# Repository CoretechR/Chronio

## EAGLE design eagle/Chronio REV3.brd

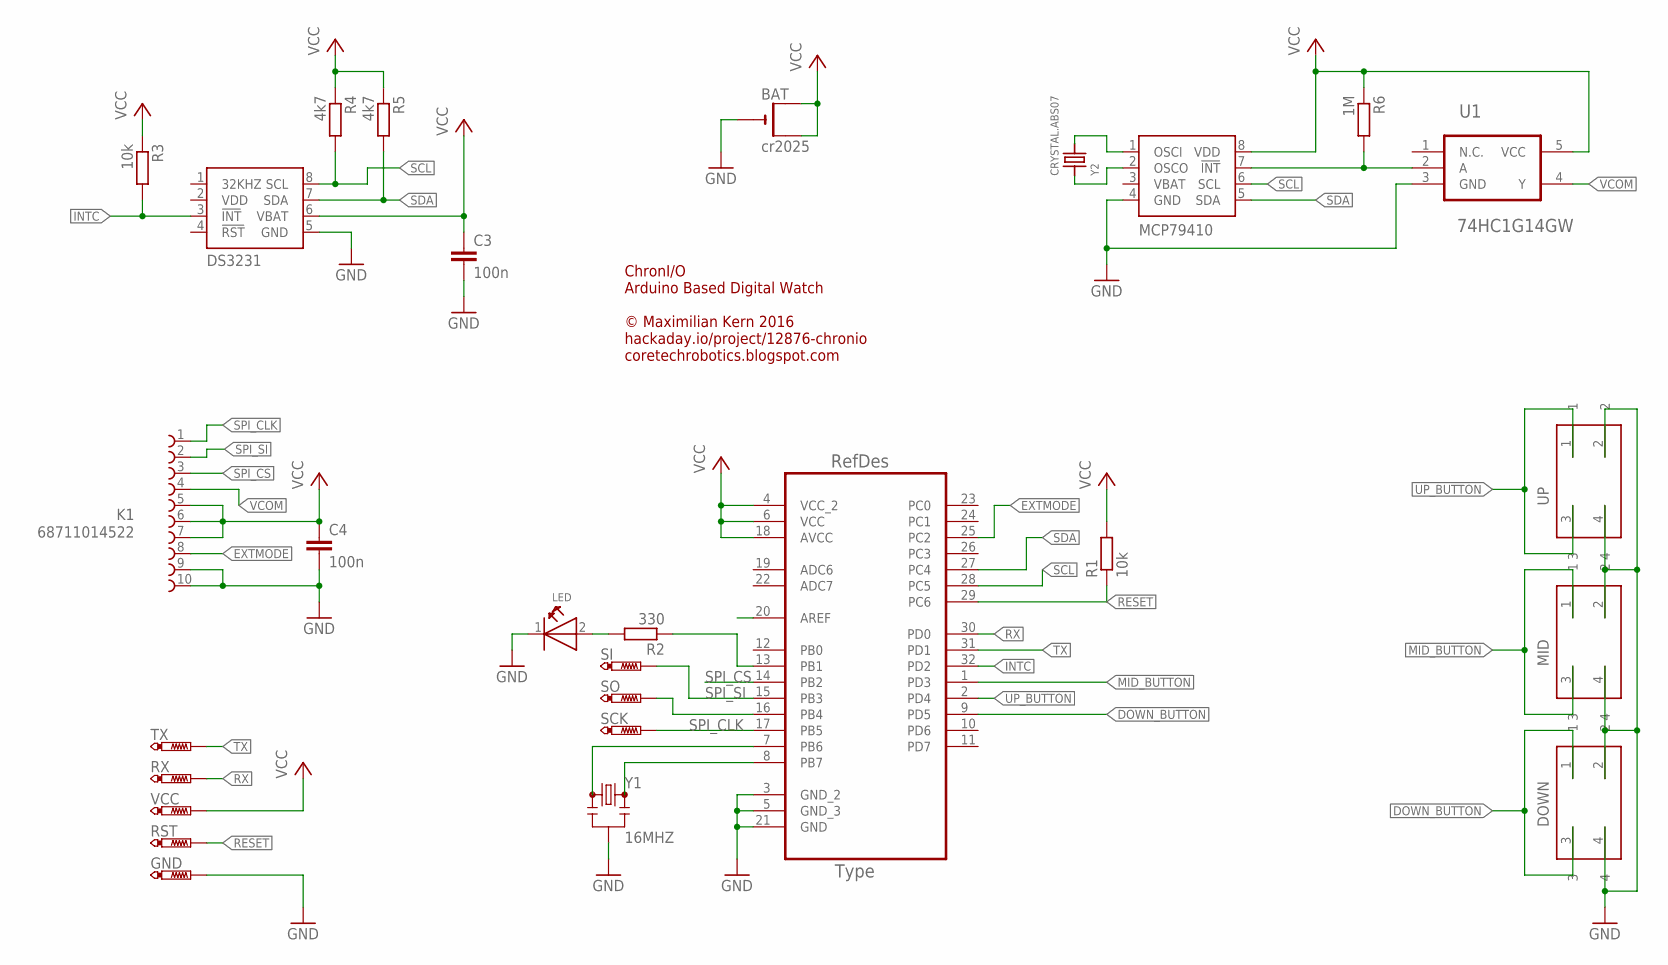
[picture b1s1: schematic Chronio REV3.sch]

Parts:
ATMEGA328P: ATMEGA328P-AU; QFP80P900X900X120-32N
BAT: cr2025; CR2032-SMD
C3, C4: 100n; C0805
DOWN: 434331045822
DS3231: DS3231MLMD; SO08
GND: PTR1TP14SQ; TP14SQ
K1: 68711014522
LED: WL-SMCW-150060GS75000-G; 0603
MCP79410: PCF8523T/1LMD; SO08
MID: 434331045822
R1, R3: 10k; R0805
R2: 330; R0805
R4, R5: 4k7; R0805
R6: 1M; R0805
RST: PTR1TP14SQ; TP14SQ
RX: PTR1TP14SQ; TP14SQ
SCK: PTR1TP14SQ; TP14SQ
SI: PTR1TP14SQ; TP14SQ
SO: PTR1TP14SQ; TP14SQ
TX: PTR1TP14SQ; TP14SQ
U1: 74HC1G14GW; SOT65P210X110-5N
UP: 434331045822
VCC: PTR1TP14SQ; TP14SQ
Y1: 16MHZ; RESONATOR-SMD
Y2: CRYSTAL.ABS07; ABS07

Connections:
AREF: ATMEGA328P.20 (AREF)
DOWN_BUTTON: ATMEGA328P.9 (PD5), DOWN.1, DOWN.3
EXTMODE: ATMEGA328P.25 (PC2), K1.8
GND: ATMEGA328P.3 (GND_2), ATMEGA328P.5 (GND_3), ATMEGA328P.21 (GND), BAT.-, C3.2, C4.2, DOWN.2, DOWN.4, DS3231.5 (GND), GND.TP, K1.9, K1.10, LED.1 (K), MCP79410.4 (GND), MID.2, MID.4, U1.3 (GND), UP.2, UP.4, Y1.2
INTC: ATMEGA328P.32 (PD2), DS3231.3 (!INT), R3.2
MID_BUTTON: ATMEGA328P.1 (PD3), MID.1, MID.3
unnamed: ATMEGA328P.7 (PB6), Y1.1
unnamed: ATMEGA328P.8 (PB7), Y1.3
unnamed: MCP79410.7 (!INT), R6.2, U1.2 (A)
unnamed: ATMEGA328P.16 (PB4), SO.TP
unnamed: MCP79410.1 (OSCI), Y2.2
unnamed: ATMEGA328P.13 (PB1), R2.1
unnamed: LED.2 (A), R2.2
unnamed: MCP79410.2 (OSCO), Y2.1
RESET: ATMEGA328P.29 (PC6), R1.1, RST.TP
RX: ATMEGA328P.30 (PD0), RX.TP
SCL: ATMEGA328P.28 (PC5), DS3231.8 (SCL), MCP79410.6 (SCL), R4.2
SDA: ATMEGA328P.27 (PC4), DS3231.7 (SDA), MCP79410.5 (SDA), R5.2
SPI_CLK: ATMEGA328P.17 (PB5), K1.1, SCK.TP
SPI_CS: ATMEGA328P.14 (PB2), K1.3
SPI_SI: ATMEGA328P.15 (PB3), K1.2, SI.TP
TX: ATMEGA328P.31 (PD1), TX.TP
UP_BUTTON: ATMEGA328P.2 (PD4), UP.1, UP.3
VBAT: MCP79410.3 (VBAT)
VCC: ATMEGA328P.4 (VCC_2), ATMEGA328P.6 (VCC), ATMEGA328P.18 (AVCC), BAT.+$1 (+), BAT.+$2 (+1), C3.1, C4.1, DS3231.6 (VBAT), K1.5, K1.6, K1.7, MCP79410.8 (VDD), R1.2, R3.1, R4.1, R5.1, R6.1, U1.5 (VCC), VCC.TP
VCOM: K1.4, U1.4 (Y)
VDD: DS3231.2 (VDD)

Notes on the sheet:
ChronI/O Arduino Based Digital Watch © Maximilian Kern 2016 hackaday.io/project/12876-chronio coretechrobotics.blogspot.com

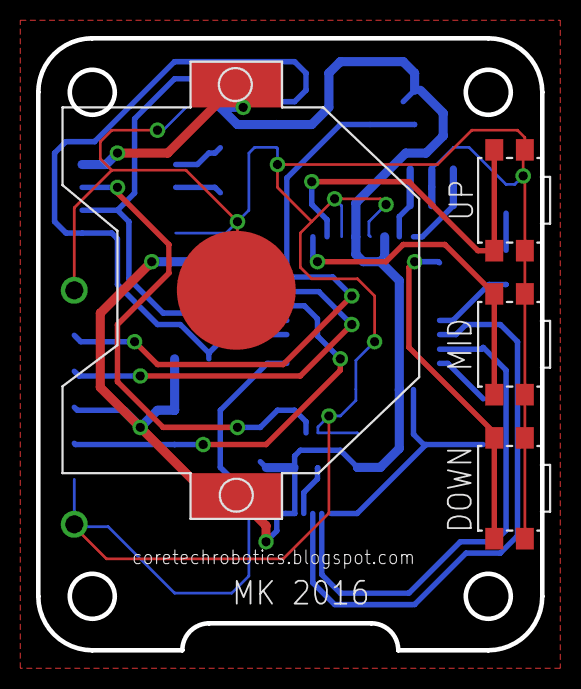
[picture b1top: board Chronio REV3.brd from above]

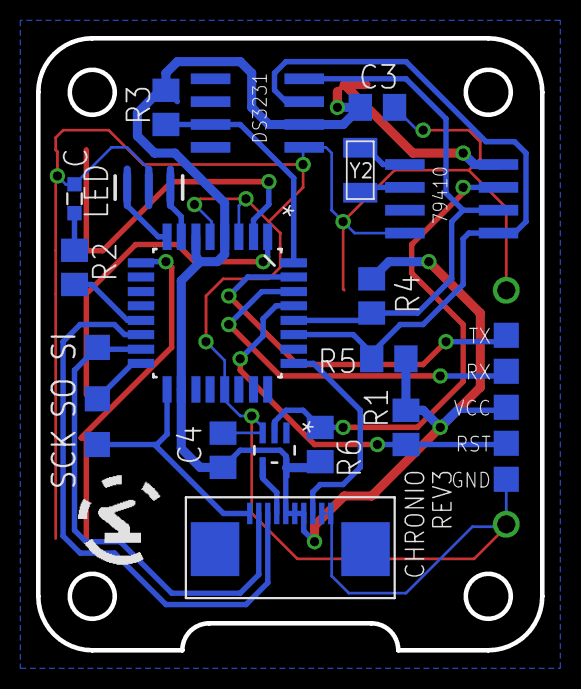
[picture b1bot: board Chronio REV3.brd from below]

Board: 2 copper layers, 28.0 x 34.0 mm, 28 parts (24 on the bottom side), 24 nets.

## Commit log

2017-01-30 :boom::camel: Added .gitattributes & .gitignore files
2017-01-30 Create LICENSE

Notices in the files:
parts and their libraries:
Eagle_FPC_CONNECTOR_AND_FFC_CAB_rev15c: Copyright: Würth Elektronik
SparkFun-FreqCtrl: Licensing: Creative Commons ShareAlike 4.0 International - https://creativecommons.org/licenses/by-sa/4.0
